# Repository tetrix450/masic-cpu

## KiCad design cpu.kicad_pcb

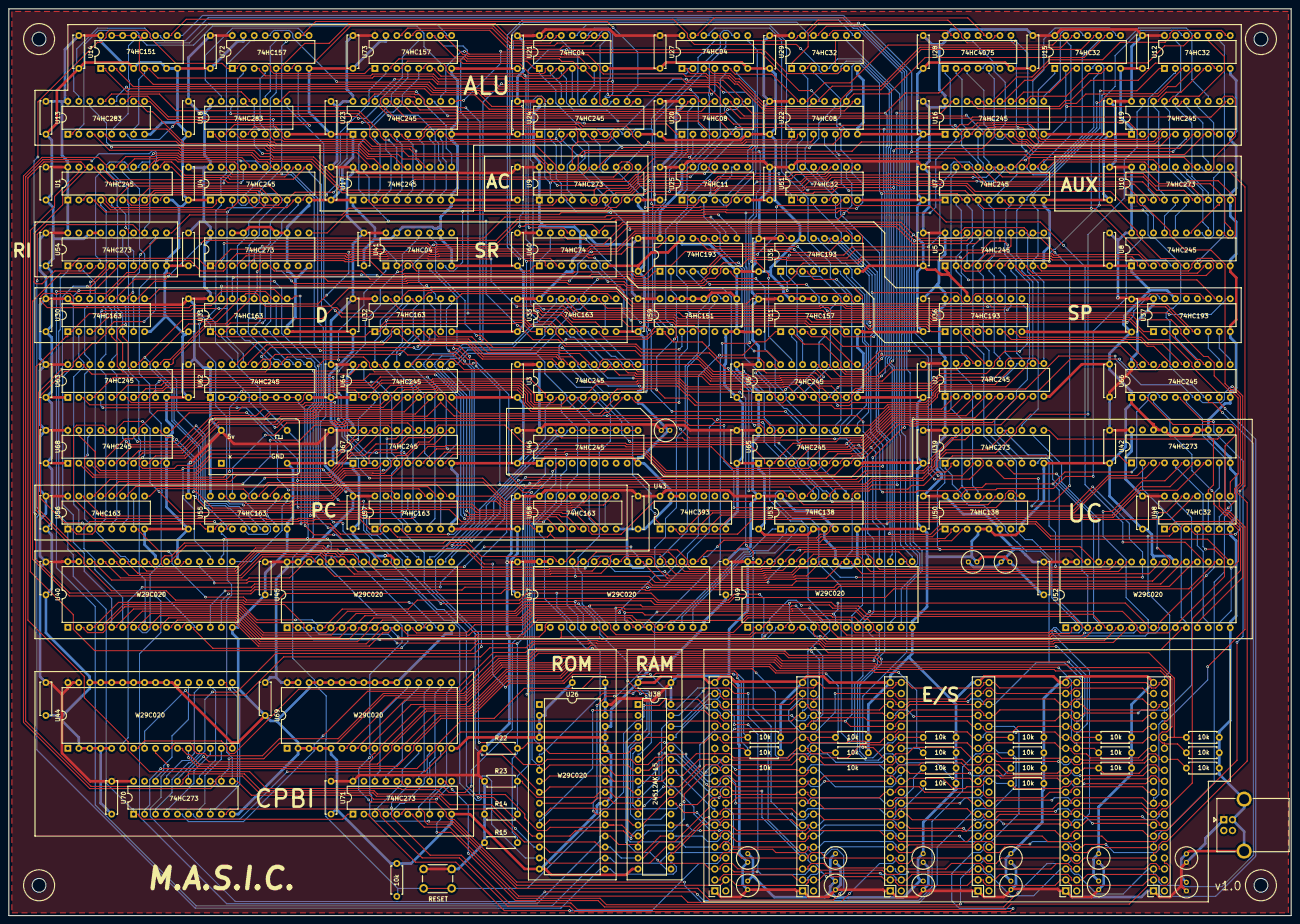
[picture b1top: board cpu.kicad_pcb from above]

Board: 2 copper layers, 297.0 x 210.0 mm, 197 parts (0 on the bottom side), 317 nets.

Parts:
C1, C2, C3, C4, C5, C6, C7, C8, C9, C10, C11, C12, C13, C14, C15, C16, C17, C18, C19, C20, C21, C22, C23, C24, C25, C26, C27, C28, C29, C30, C31, C32, C33, C34, C35, C36, C37, C39, C40, C41, C42, C43, C44, C45, C46, C47, C49, C50, C51, C52, C53, C54, C55, C56, C57, C58, C59, C60, C61, C62, C63, C64, C65, C66, C67, C68, C69, C70, C79, C84, C87, C88, C89: 100n; C_Disc_7.62mm
C38, C71, C72, C73, C74, C80, C81, C85: 1u; C_Radial_D5.0mm_H5.0mm_P2.00mm
C75, C76, C77, C78, C82, C83, C86: 10u; C_Radial_D5.0mm_H5.0mm_P2.00mm
H1, H2, H3, H4: MountingHole; MountingHole_3.2mm_M3
J0, J1, J2, J3, J4, J5: Conn_02x20_Counter_Clockwise; PinSocket_2x20_P2.54mm_Vertical
J9: USB_B; USB_B_OST_USB-B1HSxx_Horizontal
R1, R2, R3, R4, R5, R6, R7, R8, R9, R10, R11, R12, R13, R16, R17, R18, R19, R20, R21, R22, R23: 10k; R_Axial_DIN0207_L6.3mm_D2.5mm_P7.62mm_Horizontal
R14, R15: 1k; R_Axial_DIN0207_L6.3mm_D2.5mm_P7.62mm_Horizontal
SW1: SW_Push; SW_PUSH_6mm
U1, U2, U3, U4, U5, U6, U7, U8, U16, U17, U19, U23, U24, U46, U62, U63, U64, U65, U66, U67, U68: 74HC245; DIP-20_W7.62mm
U9, U10, U39, U42, U54, U61, U70, U71: 74HC273; DIP-20_W7.62mm
U11: 74HC157; DIP-16_W7.62mm
U12, U15, U29, U48, U51: 74HC32; DIP-14_W7.62mm
U13, U18: 74HC283; DIP-16_W7.62mm
U14, U59: 74HC151; DIP-16_W7.62mm
U20, U22: 74HC08; DIP-14_W7.62mm
U21, U27, U41: 74HC04; DIP-14_W7.62mm
U25: 74HC11; DIP-14_W7.62mm
U26, U40, U44, U45, U47, U49, U52, U69: W29C020; DIP-32_W15.24mm
U28: 74HC4075; DIP-14_W7.62mm
U30, U31, U32, U33, U55, U56, U57, U58: 74HC163; DIP-16_W7.62mm
U34, U35, U36, U37: 74HC193; DIP-16_W7.62mm
U38: 24512AK-15; DIP-32_W7.62mm
U43: 74LS393; DIP-14_W7.62mm
U50, U53: 74HC138; DIP-16_W7.62mm
U60: 74HC74; DIP-14_W7.62mm
U72, U73: 74LS157; DIP-16_W7.62mm
X1: 4MHz; Oscillator_DIP-14

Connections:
+5V: C1.1, C2.1, C3.1, C4.1, C5.1, C6.1, C7.1, C8.1, C9.1, C10.1, C11.1, C12.1, C13.1, C14.1, C15.1, C16.1, C17.1, C18.1, C19.1, C20.1, C21.1, C22.1, C23.1, C24.1, C25.1, C26.1, C27.1, C28.1, C29.1, C30.1, C31.1, C32.1, C33.1, C34.1, C35.1, C36.1, C37.1, C38.1, C39.1, C40.1, C41.1, C42.2, C43.1, C44.1, C45.1, C46.2, C47.1, C49.2, C50.1, C51.1, C52.1, C53.1, C54.1, C55.1, C56.1, C57.1, C58.1, C59.1, C60.1, C61.1, C62.1, C63.1, C64.1, C65.1, C66.1, C67.1, C68.1, C69.1, C70.1, C71.1, C72.1, C73.1, C74.1, C75.1, C76.1, C77.1, C78.1, C79.2, C80.1, C81.1, C82.1, C83.1, C84.1, C85.1, C86.1, C87.1, C88.1, C89.1, J0.1, J1.1, J2.1, J3.1, J4.1, J5.1, J9.1 (VBUS), R14.1, R15.1, R22.1, R23.1, SW1.1, U1.1 (A->B), U1.20 (VCC), U2.1 (A->B), U2.20 (VCC), U3.1 (A->B), U3.20 (VCC), U4.20 (VCC), U5.20 (VCC), U6.1 (A->B), U6.20 (VCC), U7.20 (VCC), U8.20 (VCC), U9.1 (~Mr), U9.20 (VCC), U10.1 (~Mr), U10.20 (VCC), U11.16 (VCC), U12.14 (VCC), U13.16 (VCC), U14.3 (I1), U14.16 (VCC), U15.14 (VCC), U16.20 (VCC), U17.20 (VCC), U18.16 (VCC), U19.20 (VCC), U20.14 (VCC), U21.14 (VCC), U22.14 (VCC), U23.20 (VCC), U24.20 (VCC), U25.14 (VCC), U26.31 (~WE), U26.32 (VDD), U27.14 (VCC), U28.14 (VDD), U29.14 (VCC), U30.16 (VCC), U31.16 (VCC), U32.16 (VCC), U33.16 (VCC), U34.16 (VCC), U35.16 (VCC), U36.16 (VCC), U37.16 (VCC), U38.32 (VDD), U39.20 (VCC), U40.31 (~WE), U40.32 (VDD), U41.14 (VCC), U42.20 (VCC), U43.14 (VCC), U44.31 (~WE), U44.32 (VDD), U45.31 (~WE), U45.32 (VDD), U46.20 (VCC), U47.31 (~WE), U47.32 (VDD), U48.14 (VCC), U49.31 (~WE), U49.32 (VDD), U50.6 (E3), U50.16 (VCC), U51.14 (VCC), U52.31 (~WE), U52.32 (VDD), U53.6 (E3), U53.16 (VCC), U54.20 (VCC), U55.16 (VCC), U56.16 (VCC), U57.16 (VCC), U58.16 (VCC), U59.16 (VCC), U60.4 (~S), U60.10 (~S), U60.14 (VCC), U61.20 (VCC), U62.1 (A->B), U62.20 (VCC), U63.20 (VCC), U64.20 (VCC), U65.20 (VCC), U66.20 (VCC), U67.20 (VCC), U68.20 (VCC), U69.31 (~WE), U69.32 (VDD), U70.20 (VCC), U71.20 (VCC), U72.16 (VCC), U73.16 (VCC), X1.14 (Vcc)
/CLK: J0.40, J1.40, J2.40, J3.40, J4.40, J5.40, U29.2, U29.5, U29.10, U30.2 (CP), U31.2 (CP), U32.2 (CP), U33.2 (CP), U39.11 (Cp), U41.11, U42.11 (Cp), U48.2, U48.5, U48.10, U51.5, U51.13, U55.2 (CP), U56.2 (CP), U57.2 (CP), U58.2 (CP), U70.11 (Cp), U71.11 (Cp), X1.8 (OUT)
/CPBI/BACK0: J0.32, U70.2 (Q0)
/CPBI/BACK1: J1.32, U70.5 (Q1)
/CPBI/BACK2: J2.32, U70.6 (Q2)
/CPBI/BACK3: J3.32, U70.9 (Q3)
/CPBI/BACK4: J4.32, U70.12 (Q4)
/CPBI/BACK5: J5.32, U70.15 (Q5)
/CPBI/BRQ0: J0.30, R9.1, U44.12 (A0)
/CPBI/BRQ1: J1.30, R8.1, U44.11 (A1)
/CPBI/BRQ2: J2.30, R10.1, U44.10 (A2)
/CPBI/BRQ3: J3.30, R11.1, U44.9 (A3)
/CPBI/BRQ4: J4.30, R12.1, U44.8 (A4)
/CPBI/BRQ5: J5.30, R13.1, U44.7 (A5)
/CPBI/CPUBRQ: U39.14 (D5), U70.16 (Q6)
/CPBI/CPUIRQ: U39.17 (D6), U71.16 (Q6)
/CPBI/IACK0: J0.8, U71.2 (Q0)
/CPBI/IACK1: J1.8, U71.5 (Q1)
/CPBI/IACK2: J2.8, U71.6 (Q2)
/CPBI/IACK3: J3.8, U71.9 (Q3)
/CPBI/IACK4: J4.8, U71.12 (Q4)
/CPBI/IACK5: J5.8, U71.15 (Q5)
/CPBI/IRQ0: J0.28, R3.1, U69.12 (A0)
/CPBI/IRQ1: J1.28, R2.1, U69.11 (A1)
/CPBI/IRQ2: J2.28, R4.1, U69.10 (A2)
/CPBI/IRQ3: J3.28, R5.1, U69.9 (A3)
/CPBI/IRQ4: J4.28, R6.1, U69.8 (A4)
/CPBI/IRQ5: J5.28, R7.1, U69.7 (A5)
/CPU/AC_0: U7.18 (B0), U9.2 (Q0), U10.3 (D0), U12.2, U13.5 (A1), U14.12 (I7), U14.13 (I6), U14.14 (I5), U14.15 (I4), U20.2
/CPU/AC_1: U7.17 (B1), U9.5 (Q1), U10.4 (D1), U12.5, U13.3 (A2), U19.18 (B0), U20.5
/CPU/AC_2: U7.16 (B2), U9.6 (Q2), U10.7 (D2), U12.10, U13.14 (A3), U19.17 (B1), U20.10
/CPU/AC_3: U7.15 (B3), U9.9 (Q3), U10.8 (D3), U12.13, U13.12 (A4), U19.16 (B2), U20.13
/CPU/AC_4: U7.14 (B4), U9.12 (Q4), U10.13 (D4), U15.2, U18.5 (A1), U19.15 (B3), U22.2
/CPU/AC_5: U7.13 (B5), U9.15 (Q5), U10.14 (D5), U15.5, U18.3 (A2), U19.14 (B4), U22.5
/CPU/AC_6: U7.12 (B6), U9.16 (Q6), U10.17 (D6), U15.10, U18.14 (A3), U19.13 (B5), U22.10
/CPU/AC_7: U7.11 (B7), U9.19 (Q7), U10.18 (D7), U14.1 (I3), U15.13, U18.12 (A4), U19.12 (B6), U22.13, U25.13, U27.5
/CPU/ALU/NOT_0: U21.2, U24.18 (B0), U73.3 (I1a)
/CPU/ALU/NOT_1: U21.4, U24.17 (B1), U73.6 (I1b)
/CPU/ALU/NOT_2: U21.6, U24.16 (B2), U73.10 (I1c)
/CPU/ALU/NOT_3: U21.8, U24.15 (B3), U73.13 (I1d)
/CPU/ALU/NOT_4: U21.10, U24.14 (B4), U72.3 (I1a)
/CPU/ALU/NOT_5: U21.12, U24.13 (B5), U72.6 (I1b)
/CPU/ALU/NOT_6: U24.12 (B6), U27.2, U72.10 (I1c)
/CPU/ALU/NOT_7: U24.11 (B7), U27.4, U72.13 (I1d)
/CPU/ALU/TO_AC_0: U6.18 (B0), U9.3 (D0), U16.2 (A0), U17.2 (A0), U19.2 (A0), U23.2 (A0), U24.2 (A0), U28.1
/CPU/ALU/TO_AC_1: U6.17 (B1), U9.4 (D1), U16.3 (A1), U17.3 (A1), U19.3 (A1), U23.3 (A1), U24.3 (A1), U28.2
/CPU/ALU/TO_AC_2: U6.16 (B2), U9.7 (D2), U16.4 (A2), U17.4 (A2), U19.4 (A2), U23.4 (A2), U24.4 (A2), U28.8
/CPU/ALU/TO_AC_3: U6.15 (B3), U9.8 (D3), U16.5 (A3), U17.5 (A3), U19.5 (A3), U23.5 (A3), U24.5 (A3), U28.3
/CPU/ALU/TO_AC_4: U6.14 (B4), U9.13 (D4), U16.6 (A4), U17.6 (A4), U19.6 (A4), U23.6 (A4), U24.6 (A4), U28.4
/CPU/ALU/TO_AC_5: U6.13 (B5), U9.14 (D5), U16.7 (A5), U17.7 (A5), U19.7 (A5), U23.7 (A5), U24.7 (A5), U28.5
/CPU/ALU/TO_AC_6: U6.12 (B6), U9.17 (D6), U16.8 (A6), U17.8 (A6), U19.8 (A6), U23.8 (A6), U24.8 (A6), U29.12
/CPU/ALU/TO_ADDER_0: U13.6 (B1), U73.4 (Za)
/CPU/ALU/TO_ADDER_1: U13.2 (B2), U73.7 (Zb)
/CPU/ALU/TO_ADDER_2: U13.15 (B3), U73.9 (Zc)
/CPU/ALU/TO_ADDER_3: U13.11 (B4), U73.12 (Zd)
/CPU/ALU/TO_ADDER_4: U18.6 (B1), U72.4 (Za)
/CPU/ALU/TO_ADDER_5: U18.2 (B2), U72.7 (Zb)
/CPU/ALU/TO_ADDER_6: U18.15 (B3), U72.9 (Zc)
/CPU/ALU/TO_ADDER_7: U18.11 (B4), U72.12 (Zd)
/CPU/ALU_C: U18.9 (C4), U59.3 (I1), U59.4 (I0)
/CPU/ALU_O: U11.6 (I1b), U51.3
/CPU/ALU_S: U6.11 (B7), U9.18 (D7), U11.3 (I1a), U16.9 (A7), U17.9 (A7), U19.9 (A7), U23.9 (A7), U24.9 (A7), U25.3, U27.11, U29.13
/CPU/ALU_Z: U11.10 (I1c), U27.12
/CPU/AUX0: U8.18 (B0), U10.2 (Q0)
/CPU/AUX1: U8.17 (B1), U10.5 (Q1)
/CPU/AUX2: U8.16 (B2), U10.6 (Q2)
/CPU/AUX3: U8.15 (B3), U10.9 (Q3)
/CPU/AUX4: U8.14 (B4), U10.12 (Q4)
/CPU/AUX5: U8.13 (B5), U10.15 (Q5)
/CPU/AUX6: U8.12 (B6), U10.16 (Q6)
/CPU/AUX7: U8.11 (B7), U10.19 (Q7)
/CPU/BACK: U44.6 (A6), U52.21 (DQ7)
/CPU/BUS_0: U1.2 (A0), U2.18 (B0), U3.18 (B0), U4.2 (A0), U5.2 (A0), U6.2 (A0), U7.2 (A0), U8.2 (A0), U15.12, U22.12, U25.2, U27.3, U27.9, U30.3 (D0), U32.3 (D0), U59.1 (I3), U62.18 (B0), U72.14 (I0d)
/CPU/BUS_1: U1.3 (A1), U2.17 (B1), U3.17 (B1), U4.3 (A1), U5.3 (A1), U6.3 (A1), U7.3 (A1), U8.3 (A1), U11.2 (I0a), U15.9, U22.9, U27.1, U30.4 (D1), U32.4 (D1), U62.17 (B1), U72.11 (I0c)
/CPU/BUS_2: U1.4 (A2), U2.16 (B2), U3.16 (B2), U4.4 (A2), U5.4 (A2), U6.4 (A2), U7.4 (A2), U8.4 (A2), U11.5 (I0b), U15.4, U21.13, U22.4, U30.5 (D2), U32.5 (D2), U62.16 (B2), U72.5 (I0b)
/CPU/BUS_3: U1.5 (A3), U2.15 (B3), U3.15 (B3), U4.5 (A3), U5.5 (A3), U6.5 (A3), U7.5 (A3), U8.5 (A3), U11.11 (I0c), U15.1, U21.11, U22.1, U30.6 (D3), U32.6 (D3), U62.15 (B3), U72.2 (I0a)
/CPU/BUS_4: U1.6 (A4), U2.14 (B4), U3.14 (B4), U4.6 (A4), U5.6 (A4), U6.6 (A4), U7.6 (A4), U8.6 (A4), U12.12, U20.12, U21.9, U31.3 (D0), U33.3 (D0), U60.2 (D), U62.14 (B4), U73.14 (I0d)
/CPU/BUS_5: U1.7 (A5), U2.13 (B5), U3.13 (B5), U4.7 (A5), U5.7 (A5), U6.7 (A5), U7.7 (A5), U8.7 (A5), U12.9, U20.9, U21.5, U31.4 (D1), U33.4 (D1), U62.13 (B5), U73.11 (I0c)
/CPU/BUS_6: U1.8 (A6), U2.12 (B6), U3.12 (B6), U4.8 (A6), U5.8 (A6), U6.8 (A6), U7.8 (A6), U8.8 (A6), U12.4, U20.4, U21.3, U31.5 (D2), U33.5 (D2), U62.12 (B6), U73.5 (I0b)
/CPU/BUS_7: U1.9 (A7), U2.11 (B7), U3.11 (B7), U4.9 (A7), U5.9 (A7), U6.9 (A7), U7.9 (A7), U8.9 (A7), U12.1, U20.1, U21.1, U31.6 (D3), U33.6 (D3), U59.2 (I2), U62.11 (B7), U73.2 (I0a)
/CPU/C_FLAG: U5.18 (B0), U14.2 (I2), U39.3 (D0), U60.9 (Q)
/CPU/D0: U30.14 (Q0), U34.15 (A), U56.3 (D0), U63.18 (B0)
/CPU/D1: U30.13 (Q1), U34.1 (B), U56.4 (D1), U63.17 (B1)
/CPU/D2: U30.12 (Q2), U34.10 (C), U56.5 (D2), U63.16 (B2)
/CPU/D3: U30.11 (Q3), U34.9 (D), U56.6 (D3), U63.15 (B3)
/CPU/D4: U31.14 (Q0), U35.15 (A), U55.3 (D0), U63.14 (B4)
/CPU/D5: U31.13 (Q1), U35.1 (B), U55.4 (D1), U63.13 (B5)
/CPU/D6: U31.12 (Q2), U35.10 (C), U55.5 (D2), U63.12 (B6)
/CPU/D7: U31.11 (Q3), U35.9 (D), U55.6 (D3), U63.11 (B7)
/CPU/D8: U32.14 (Q0), U36.15 (A), U57.3 (D0), U64.18 (B0)
/CPU/D9: U32.13 (Q1), U36.1 (B), U57.4 (D1), U64.17 (B1)
/CPU/D10: U32.12 (Q2), U36.10 (C), U57.5 (D2), U64.16 (B2)
/CPU/D11: U32.11 (Q3), U36.9 (D), U57.6 (D3), U64.15 (B3)
/CPU/D12: U33.14 (Q0), U37.15 (A), U58.3 (D0), U64.14 (B4)
/CPU/D13: U33.13 (Q1), U37.1 (B), U58.4 (D1), U64.13 (B5)
/CPU/D14: U33.12 (Q2), U37.10 (C), U58.5 (D2), U64.12 (B6)
/CPU/D15: U33.11 (Q3), U37.9 (D), U58.6 (D3), U64.11 (B7)
/CPU/DAT_0: J0.26, J1.26, J2.26, J3.26, J4.26, J5.26, R21.1, U1.18 (B0), U4.18 (B0), U26.21 (DQ7), U38.13 (DQ0), U54.3 (D0)
/CPU/DAT_1: J0.24, J1.24, J2.24, J3.24, J4.24, J5.24, R20.1, U1.17 (B1), U4.17 (B1), U26.20 (DQ6), U38.14 (DQ1), U54.4 (D1)
/CPU/DAT_2: J0.22, J1.22, J2.22, J3.22, J4.22, J5.22, R19.1, U1.16 (B2), U4.16 (B2), U26.19 (DQ5), U38.15 (DQ2), U54.7 (D2)
/CPU/DAT_3: J0.18, J1.18, J2.18, J3.18, J4.18, J5.18, R18.1, U1.15 (B3), U4.15 (B3), U26.18 (DQ4), U38.17 (DQ3), U54.8 (D3)
/CPU/DAT_4: J0.16, J1.16, J2.16, J3.16, J4.16, J5.16, R17.1, U1.14 (B4), U4.14 (B4), U26.17 (DQ3), U38.18 (DQ4), U54.13 (D4)
/CPU/DAT_5: J0.14, J1.14, J2.14, J3.14, J4.14, J5.14, R16.1, U1.13 (B5), U4.13 (B5), U26.15 (DQ2), U38.19 (DQ5), U54.14 (D5)
/CPU/DAT_6: J0.12, J1.12, J2.12, J3.12, J4.12, J5.12, U1.12 (B6), U4.12 (B6), U26.14 (DQ1), U38.20 (DQ6)
/CPU/DAT_7: J0.10, J1.10, J2.10, J3.10, J4.10, J5.10, U1.11 (B7), U4.11 (B7), U26.13 (DQ0), U38.21 (DQ7)
/CPU/DIR_0: J0.33, J1.33, J2.33, J3.33, J4.33, J5.33, U2.2 (A0), U26.12 (A0), U38.12 (A0), U63.2 (A0), U65.2 (A0), U67.2 (A0)
/CPU/DIR_1: J0.31, J1.31, J2.31, J3.31, J4.31, J5.31, U2.3 (A1), U26.11 (A1), U38.11 (A1), U63.3 (A1), U65.3 (A1), U67.3 (A1)
/CPU/DIR_2: J0.29, J1.29, J2.29, J3.29, J4.29, J5.29, U2.4 (A2), U26.10 (A2), U38.10 (A2), U63.4 (A2), U65.4 (A2), U67.4 (A2)
/CPU/DIR_3: J0.27, J1.27, J2.27, J3.27, J4.27, J5.27, U2.5 (A3), U26.9 (A3), U38.9 (A3), U63.5 (A3), U65.5 (A3), U67.5 (A3)
/CPU/DIR_4: J0.25, J1.25, J2.25, J3.25, J4.25, J5.25, U2.6 (A4), U26.8 (A4), U38.8 (A4), U63.6 (A4), U65.6 (A4), U67.6 (A4)
/CPU/DIR_5: J0.23, J1.23, J2.23, J3.23, J4.23, J5.23, U2.7 (A5), U26.7 (A5), U38.7 (A5), U63.7 (A5), U65.7 (A5), U67.7 (A5)
/CPU/DIR_6: J0.21, J1.21, J2.21, J3.21, J4.21, J5.21, U2.8 (A6), U26.6 (A6), U38.6 (A6), U63.8 (A6), U65.8 (A6), U67.8 (A6)
/CPU/DIR_7: J0.19, J1.19, J2.19, J3.19, J4.19, J5.19, U2.9 (A7), U26.5 (A7), U38.5 (A7), U63.9 (A7), U65.9 (A7), U67.9 (A7)
/CPU/DIR_8: J0.17, J1.17, J2.17, J3.17, J4.17, J5.17, U3.2 (A0), U26.27 (A8), U38.27 (A8), U64.2 (A0), U66.2 (A0), U68.2 (A0)
/CPU/DIR_9: J0.15, J1.15, J2.15, J3.15, J4.15, J5.15, U3.3 (A1), U26.26 (A9), U38.26 (A9), U64.3 (A1), U66.3 (A1), U68.3 (A1)
/CPU/DIR_10: J0.13, J1.13, J2.13, J3.13, J4.13, J5.13, U3.4 (A2), U38.23 (A10), U64.4 (A2), U66.4 (A2), U68.4 (A2)
/CPU/DIR_11: J0.11, J1.11, J2.11, J3.11, J4.11, J5.11, U3.5 (A3), U38.25 (A11), U64.5 (A3), U66.5 (A3), U68.5 (A3)
/CPU/DIR_12: J0.9, J1.9, J2.9, J3.9, J4.9, J5.9, U3.6 (A4), U38.4 (A12), U64.6 (A4), U66.6 (A4), U68.6 (A4)
/CPU/DIR_13: J0.7, J1.7, J2.7, J3.7, J4.7, J5.7, U3.7 (A5), U25.11, U38.28 (A13), U64.7 (A5), U66.7 (A5), U68.7 (A5)
/CPU/DIR_14: J0.5, J1.5, J2.5, J3.5, J4.5, J5.5, U3.8 (A6), U25.10, U38.3 (A14), U64.8 (A6), U66.8 (A6), U68.8 (A6)
/CPU/DIR_15: J0.3, J1.3, J2.3, J3.3, J4.3, J5.3, U3.9 (A7), U25.9, U38.31 (A15), U64.9 (A7), U66.9 (A7), U68.9 (A7)
/CPU/FILL_BIT: U45.14 (DQ1), U62.2 (A0), U62.3 (A1), U62.4 (A2), U62.5 (A3), U62.6 (A4), U62.7 (A5), U62.8 (A6), U62.9 (A7)
/CPU/F_AC: U9.11 (Cp), U48.6
/CPU/F_AUX: U10.11 (Cp), U48.3
/CPU/F_C: U29.6, U60.11 (C)
/CPU/F_DH: U32.9 (~PE), U33.9 (~PE), U45.19 (DQ5)
/CPU/F_DL: U30.9 (~PE), U31.9 (~PE), U45.20 (DQ6)
/CPU/F_D_UP: U30.7 (CEP), U30.10 (CET), U52.18 (DQ4)
/CPU/F_I: U29.8, U60.3 (C)
/CPU/F_PC: U40.17 (DQ3), U55.9 (~PE), U56.9 (~PE), U57.9 (~PE), U58.9 (~PE)
/CPU/F_PC_UP: U52.20 (DQ6), U56.7 (CEP), U56.10 (CET)
/CPU/F_RI: U51.11, U54.11 (Cp)
/CPU/F_SP_DOWN: U34.4 (DOWN), U48.8
/CPU/F_SP_UP: U34.5 (UP), U51.6
/CPU/F_ZOS: U29.3, U61.11 (Cp)
/CPU/IACK: U49.13 (DQ0), U69.6 (A6)
/CPU/I_FLAG: U5.11 (B7), U5.12 (B6), U5.13 (B5), U5.14 (B4), U39.13 (D4), U60.5 (Q)
/CPU/MUX C/C: U59.5 (Z), U60.12 (D)
/CPU/MUX ZOS/O: U11.7 (Zb), U61.4 (D1)
/CPU/MUX ZOS/S: U11.4 (Za), U61.3 (D0)
/CPU/MUX ZOS/Z: U11.9 (Zc), U61.7 (D2)
/CPU/MUX_ADD: U40.13 (DQ0), U72.1 (S), U73.1 (S)
/CPU/MUX_CI_0: U14.11 (S0), U49.18 (DQ4)
/CPU/MUX_CI_1: U14.10 (S1), U49.19 (DQ5)
/CPU/MUX_CI_2: U14.9 (S2), U49.20 (DQ6)
/CPU/MUX_C_0: U47.20 (DQ6), U59.10 (S1)
/CPU/MUX_C_1: U47.21 (DQ7), U59.11 (S0)
/CPU/MUX_ZOS: U11.1 (S), U45.13 (DQ0)
/CPU/O_FLAG: U5.16 (B2), U39.7 (D2), U61.5 (Q1)
/CPU/PC_0: U56.14 (Q0), U67.18 (B0)
/CPU/PC_1: U56.13 (Q1), U67.17 (B1)
/CPU/PC_2: U56.12 (Q2), U67.16 (B2)
/CPU/PC_3: U56.11 (Q3), U67.15 (B3)
/CPU/PC_4: U55.14 (Q0), U67.14 (B4)
/CPU/PC_5: U55.13 (Q1), U67.13 (B5)
/CPU/PC_6: U55.12 (Q2), U67.12 (B6)
/CPU/PC_7: U55.11 (Q3), U67.11 (B7)
/CPU/PC_8: U57.14 (Q0), U68.18 (B0)
/CPU/PC_9: U57.13 (Q1), U68.17 (B1)
/CPU/PC_10: U57.12 (Q2), U68.16 (B2)
/CPU/PC_11: U57.11 (Q3), U68.15 (B3)
/CPU/PC_12: U58.14 (Q0), U68.14 (B4)
/CPU/PC_13: U58.13 (Q1), U68.13 (B5)
/CPU/PC_14: U58.12 (Q2), U68.12 (B6)
/CPU/PC_15: U58.11 (Q3), U68.11 (B7)
/CPU/RI0: U40.26 (A9), U45.26 (A9), U47.26 (A9), U49.26 (A9), U52.26 (A9), U54.2 (Q0)
/CPU/RI1: U40.27 (A8), U45.27 (A8), U47.27 (A8), U49.27 (A8), U52.27 (A8), U54.5 (Q1)
/CPU/RI2: U40.5 (A7), U45.5 (A7), U47.5 (A7), U49.5 (A7), U52.5 (A7), U54.6 (Q2)
/CPU/RI3: U40.6 (A6), U45.6 (A6), U47.6 (A6), U49.6 (A6), U52.6 (A6), U54.9 (Q3)
/CPU/RI4: U40.7 (A5), U45.7 (A5), U47.7 (A5), U49.7 (A5), U52.7 (A5), U54.12 (Q4)
/CPU/RI5: U40.8 (A4), U45.8 (A4), U47.8 (A4), U49.8 (A4), U52.8 (A4), U54.15 (Q5)
/CPU/SP_0: U34.3 (QA), U65.18 (B0)
/CPU/SP_1: U34.2 (QB), U65.17 (B1)
/CPU/SP_2: U34.6 (QC), U65.16 (B2)
/CPU/SP_3: U34.7 (QD), U65.15 (B3)
/CPU/SP_4: U35.3 (QA), U65.14 (B4)
/CPU/SP_5: U35.2 (QB), U65.13 (B5)
/CPU/SP_6: U35.6 (QC), U65.12 (B6)
/CPU/SP_7: U35.7 (QD), U65.11 (B7)
/CPU/SP_8: U36.3 (QA), U66.18 (B0)
/CPU/SP_9: U36.2 (QB), U66.17 (B1)
/CPU/SP_10: U36.6 (QC), U66.16 (B2)
/CPU/SP_11: U36.7 (QD), U66.15 (B3)
/CPU/SP_12: U37.3 (QA), U66.14 (B4)
/CPU/SP_13: U37.2 (QB), U66.13 (B5)
/CPU/SP_14: U37.6 (QC), U66.12 (B6)
/CPU/SP_15: U37.7 (QD), U66.11 (B7)
/CPU/S_FLAG: U5.17 (B1), U39.4 (D1), U61.2 (Q0)
/CPU/Unidad de control/BUS_DIS: U46.19 (CE), U49.21 (DQ7)
/CPU/Unidad de control/IFETCH: U39.18 (D7), U40.21 (DQ7)
/CPU/Unidad de control/RCF_0: U42.3 (D0), U43.3 (Q0)
/CPU/Unidad de control/RCF_1: U42.4 (D1), U43.4 (Q1)
/CPU/Unidad de control/RCF_2: U42.7 (D2), U43.5 (Q2)
/CPU/Unidad de control/RCF_3: U42.8 (D3), U43.6 (Q3)
/CPU/Unidad de control/RCF_CLR: U40.20 (DQ6), U48.12
/CPU/Unidad de control/S_AC_0: U47.13 (DQ0), U53.1 (A0)
/CPU/Unidad de control/S_AC_1: U47.14 (DQ1), U53.2 (A1)
/CPU/Unidad de control/S_AC_2: U47.15 (DQ2), U53.3 (A2)
/CPU/Unidad de control/S_DAT_0: U47.17 (DQ3), U50.1 (A0)
/CPU/Unidad de control/S_DAT_1: U47.18 (DQ4), U50.2 (A1)
/CPU/Unidad de control/S_DAT_2: U47.19 (DQ5), U50.3 (A2)
/CPU/Unidad de control/~AC_LOAD: U48.4, U52.14 (DQ1)
/CPU/Unidad de control/~AUX_LOAD: U48.1, U52.15 (DQ2)
/CPU/Unidad de control/~LOAD_C: U29.4, U49.14 (DQ1)
/CPU/Unidad de control/~LOAD_I: U29.9, U49.17 (DQ3)
/CPU/Unidad de control/~LOAD_ZOS: U29.1, U49.15 (DQ2)
/CPU/Unidad de control/~RI_LOAD: U51.12, U52.17 (DQ3)
/CPU/Unidad de control/~SP_DOWN: U48.9, U52.13 (DQ0)
/CPU/Unidad de control/~SP_UP: U51.4, U52.19 (DQ5)
/CPU/Z_FLAG: U5.15 (B3), U39.8 (D3), U61.6 (Q2)
/CPU/~AC_OE: U7.19 (CE), U50.14 (O1)
/CPU/~ADD_OE: U17.19 (CE), U53.15 (O0)
/CPU/~AND_OE: U23.19 (CE), U53.13 (O2)
/CPU/~AUX_OE: U8.19 (CE), U50.15 (O0)
/CPU/~BUS_AC: U6.19 (CE), U53.10 (O5)
/CPU/~DIRH_OE: U3.19 (CE), U50.12 (O3)
/CPU/~DIRL_OE: U2.19 (CE), U50.13 (O2)
/CPU/~D_CLR: U30.1 (~MR), U31.1 (~MR), U32.1 (~MR), U33.1 (~MR), U45.15 (DQ2)
/CPU/~D_OE: U45.21 (DQ7), U63.19 (CE), U64.19 (CE)
/CPU/~EST_OE: U5.19 (CE), U50.10 (O5)
/CPU/~FILL_BUS: U50.9 (O6), U62.19 (CE)
/CPU/~MEM_BUS: U4.19 (CE), U50.11 (O4)
/CPU/~MEM_OE: J0.37, J1.37, J2.37, J3.37, J4.37, J5.37, R14.2, R23.2, U26.24 (~OE), U38.24 (~OE), U46.3 (A1)
/CPU/~MEM_WE: J0.35, J1.35, J2.35, J3.35, J4.35, J5.35, R15.2, R22.2, U1.19 (CE), U38.29 (~WE), U46.2 (A0)
/CPU/~NOT_OE: U24.19 (CE), U53.11 (O4)
/CPU/~OR_OE: U16.19 (CE), U53.12 (O3)
/CPU/~PC_OE: U40.19 (DQ5), U67.19 (CE), U68.19 (CE)
/CPU/~SHR_OE: U19.19 (CE), U53.14 (O1)
/CPU/~SP_LOAD: U34.11 (~LOAD), U35.11 (~LOAD), U36.11 (~LOAD), U37.11 (~LOAD), U40.14 (DQ1)
/CPU/~SP_OE: U40.15 (DQ2), U65.19 (CE), U66.19 (CE)
/Decoficación mapa memoria/~CE_BOOTLOADER: U41.6, U51.10
/Decoficación mapa memoria/~CE_RAM: U25.8, U38.22 (~CE1), U41.5
GND: C1.2, C2.2, C3.2, C4.2, C5.2, C6.2, C7.2, C8.2, C9.2, C10.2, C11.2, C12.2, C13.2, C14.2, C15.2, C16.2, C17.2, C18.2, C19.2, C20.2, C21.2, C22.2, C23.2, C24.2, C25.2, C26.2, C27.2, C28.2, C29.2, C30.2, C31.2, C32.2, C33.2, C34.2, C35.2, C36.2, C37.2, C38.2, C39.2, C40.2, C41.2, C42.1, C43.2, C44.2, C45.2, C46.1, C47.2, C49.1, C50.2, C51.2, C52.2, C53.2, C54.2, C55.2, C56.2, C57.2, C58.2, C59.2, C60.2, C61.2, C62.2, C63.2, C64.2, C65.2, C66.2, C67.2, C68.2, C69.2, C70.2, C71.2, C72.2, C73.2, C74.2, C75.2, C76.2, C77.2, C78.2, C79.1, C80.2, C81.2, C82.2, C83.2, C84.2, C85.2, C86.2, C87.2, C88.2, C89.2, J0.39, J1.39, J2.39, J3.39, J4.39, J5.39, J9.4 (GND), J9.5 (Shield), R1.2, R2.2, R3.2, R4.2, R5.2, R6.2, R7.2, R8.2, R9.2, R10.2, R11.2, R12.2, R13.2, R16.2, R17.2, R18.2, R19.2, R20.2, R21.2, U1.10 (GND), U2.10 (GND), U3.10 (GND), U4.1 (A->B), U4.10 (GND), U5.1 (A->B), U5.10 (GND), U6.10 (GND), U7.1 (A->B), U7.10 (GND), U8.1 (A->B), U8.10 (GND), U9.10 (GND), U10.10 (GND), U11.8 (GND), U11.13 (I1d), U11.14 (I0d), U11.15 (E), U12.7 (GND), U13.8 (GND), U14.4 (I0), U14.7 (~E), U14.8 (GND), U15.7 (GND), U16.1 (A->B), U16.10 (GND), U17.1 (A->B), U17.10 (GND), U18.8 (GND), U19.1 (A->B), U19.10 (GND), U20.7 (GND), U21.7 (GND), U22.7 (GND), U23.1 (A->B), U23.10 (GND), U24.1 (A->B), U24.10 (GND), U25.7 (GND), U26.2 (A16), U26.3 (A15), U26.4 (A12), U26.16 (GND), U26.23 (A10), U26.25 (A11), U26.28 (A13), U26.29 (A14), U26.30 (A17), U27.7 (GND), U28.7 (VSS), U29.7 (GND), U30.8 (GND), U31.8 (GND), U32.8 (GND), U33.8 (GND), U34.8 (GND), U34.14 (CLR), U35.8 (GND), U35.14 (CLR), U36.8 (GND), U36.14 (CLR), U37.8 (GND), U37.14 (CLR), U38.16 (GND), U39.10 (GND), U40.16 (GND), U40.22 (~CE), U40.24 (~OE), U41.7 (GND), U41.9, U41.13, U42.10 (GND), U42.13 (D4), U42.14 (D5), U42.17 (D6), U42.18 (D7), U43.7 (GND), U43.12 (MR), U43.13 (CP), U44.2 (A16), U44.3 (A15), U44.4 (A12), U44.5 (A7), U44.16 (GND), U44.22 (~CE), U44.23 (A10), U44.24 (~OE), U44.25 (A11), U44.26 (A9), U44.27 (A8), U44.28 (A13), U44.29 (A14), U44.30 (A17), U45.16 (GND), U45.22 (~CE), U45.24 (~OE), U46.1 (A->B), U46.10 (GND), U47.16 (GND), U47.22 (~CE), U47.24 (~OE), U48.7 (GND), U49.16 (GND), U49.22 (~CE), U49.24 (~OE), U50.4 (E1), U50.5 (E2), U50.8 (GND), U51.7 (GND), U52.16 (GND), U52.22 (~CE), U52.24 (~OE), U53.4 (E1), U53.5 (E2), U53.8 (GND), U54.10 (GND), U54.17 (D6), U54.18 (D7), U55.8 (GND), U56.8 (GND), U57.8 (GND), U58.8 (GND), U59.7 (~E), U59.8 (GND), U59.9 (S2), U59.12 (I7), U59.13 (I6), U59.14 (I5), U59.15 (I4), U60.7 (GND), U61.8 (D3), U61.10 (GND), U61.13 (D4), U61.14 (D5), U61.17 (D6), U61.18 (D7), U62.10 (GND), U63.1 (A->B), U63.10 (GND), U64.1 (A->B), U64.10 (GND), U65.1 (A->B), U65.10 (GND), U66.1 (A->B), U66.10 (GND), U67.1 (A->B), U67.10 (GND), U68.1 (A->B), U68.10 (GND), U69.2 (A16), U69.3 (A15), U69.4 (A12), U69.5 (A7), U69.16 (GND), U69.22 (~CE), U69.23 (A10), U69.24 (~OE), U69.25 (A11), U69.26 (A9), U69.27 (A8), U69.28 (A13), U69.29 (A14), U69.30 (A17), U70.10 (GND), U71.10 (GND), U72.8 (GND), U72.15 (E), U73.8 (GND), U73.15 (E), X1.7 (GND)
MEM/~IO: J0.6, J1.6, J2.6, J3.6, J4.6, J5.6, U38.30 (CE2), U41.4
unnamed: U13.7 (C0), U14.5 (Z), U19.11 (B7)
unnamed: U13.9 (C4), U18.7 (C0)
unnamed: U13.4 (S1), U17.18 (B0)
unnamed: U13.1 (S2), U17.17 (B1)
unnamed: U13.13 (S3), U17.16 (B2)
unnamed: U13.10 (S4), U17.15 (B3)
unnamed: U12.3, U16.18 (B0)
unnamed: U12.6, U16.17 (B1)
unnamed: U12.8, U16.16 (B2)
unnamed: U12.11, U16.15 (B3)
unnamed: U15.3, U16.14 (B4)
unnamed: U15.6, U16.13 (B5)
unnamed: U15.8, U16.12 (B6)
unnamed: U15.11, U16.11 (B7)
unnamed: U17.14 (B4), U18.4 (S1)
unnamed: U17.13 (B5), U18.1 (S2)
unnamed: U17.12 (B6), U18.13 (S3)
unnamed: U17.11 (B7), U18.10 (S4)
unnamed: U20.3, U23.18 (B0)
unnamed: U20.6, U23.17 (B1)
unnamed: U20.8, U23.16 (B2)
unnamed: U20.11, U23.15 (B3)
unnamed: U22.3, U23.14 (B4)
unnamed: U22.6, U23.13 (B5)
unnamed: U22.8, U23.12 (B6)
unnamed: U22.11, U23.11 (B7)
unnamed: U25.1, U27.10
unnamed: U25.4, U27.8
unnamed: U25.5, U27.6
unnamed: U25.6, U51.2
unnamed: U25.12, U51.1
unnamed: U26.22 (~CE), U51.8
unnamed: U27.13, U28.10
unnamed: U28.9, U28.11
unnamed: U28.6, U28.12
unnamed: U28.13, U29.11
unnamed: U30.15 (TC), U31.7 (CEP), U31.10 (CET)
unnamed: U31.15 (TC), U32.7 (CEP), U32.10 (CET)
unnamed: U32.15 (TC), U33.7 (CEP), U33.10 (CET)
unnamed: U34.13 (~BO), U35.4 (DOWN)
unnamed: U34.12 (~CO), U35.5 (UP)
unnamed: U35.13 (~BO), U36.4 (DOWN)
unnamed: U35.12 (~CO), U36.5 (UP)
unnamed: U36.13 (~BO), U37.4 (DOWN)
unnamed: U36.12 (~CO), U37.5 (UP)
unnamed: U39.2 (Q0), U40.23 (A10), U45.23 (A10), U47.23 (A10), U49.23 (A10), U52.23 (A10)
unnamed: U39.5 (Q1), U40.25 (A11), U45.25 (A11), U47.25 (A11), U49.25 (A11), U52.25 (A11)
unnamed: U39.6 (Q2), U40.4 (A12), U45.4 (A12), U47.4 (A12), U49.4 (A12), U52.4 (A12)
unnamed: U39.9 (Q3), U40.28 (A13), U45.28 (A13), U47.28 (A13), U49.28 (A13), U52.28 (A13)
unnamed: U39.12 (Q4), U40.29 (A14), U45.29 (A14), U47.29 (A14), U49.29 (A14), U52.29 (A14)
unnamed: U39.15 (Q5), U40.3 (A15), U45.3 (A15), U47.3 (A15), U49.3 (A15), U52.3 (A15)
unnamed: U39.16 (Q6), U40.2 (A16), U45.2 (A16), U47.2 (A16), U49.2 (A16), U52.2 (A16)
unnamed: U39.19 (Q7), U40.30 (A17), U45.30 (A17), U47.30 (A17), U49.30 (A17), U52.30 (A17)
unnamed: U40.12 (A0), U42.2 (Q0), U45.12 (A0), U47.12 (A0), U49.12 (A0), U52.12 (A0)
unnamed: U40.11 (A1), U42.5 (Q1), U45.11 (A1), U47.11 (A1), U49.11 (A1), U52.11 (A1)
unnamed: U40.10 (A2), U42.6 (Q2), U45.10 (A2), U47.10 (A2), U49.10 (A2), U52.10 (A2)
unnamed: U40.9 (A3), U42.9 (Q3), U45.9 (A3), U47.9 (A3), U49.9 (A3), U52.9 (A3)
unnamed: U43.2 (MR), U48.11
unnamed: U44.13 (DQ0), U70.3 (D0)
unnamed: U44.14 (DQ1), U70.4 (D1)
unnamed: U44.15 (DQ2), U70.7 (D2)
unnamed: U44.17 (DQ3), U70.8 (D3)
unnamed: U44.18 (DQ4), U70.13 (D4)
unnamed: U44.19 (DQ5), U70.14 (D5)
unnamed: U44.20 (DQ6), U70.17 (D6)
unnamed: U44.21 (DQ7), U70.18 (D7)
unnamed: U45.17 (DQ3), U46.11 (B7), U46.12 (B6), U46.13 (B5), U46.14 (B4), U46.15 (B3), U46.16 (B2), U46.17 (B1)
unnamed: U45.18 (DQ4), U46.18 (B0)
unnamed: U55.7 (CEP), U55.10 (CET), U56.15 (TC)
unnamed: U55.15 (TC), U57.7 (CEP), U57.10 (CET)
unnamed: U57.15 (TC), U58.7 (CEP), U58.10 (CET)
unnamed: U69.13 (DQ0), U71.3 (D0)
unnamed: U69.14 (DQ1), U71.4 (D1)
unnamed: U69.15 (DQ2), U71.7 (D2)
unnamed: U69.17 (DQ3), U71.8 (D3)
unnamed: U69.18 (DQ4), U71.13 (D4)
unnamed: U69.19 (DQ5), U71.14 (D5)
unnamed: U69.20 (DQ6), U71.17 (D6)
unnamed: U69.21 (DQ7), U71.18 (D7)
RESET: J0.34, J1.34, J2.34, J3.34, J4.34, J5.34, R1.1, SW1.2, U41.1, U48.13
~CLK: U41.10, U43.1 (CP)
~MEM/IO: J0.4, J1.4, J2.4, J3.4, J4.4, J5.4, U40.18 (DQ4), U41.3, U51.9
~RESET: J0.36, J1.36, J2.36, J3.36, J4.36, J5.36, U39.1 (~Mr), U41.2, U42.1 (~Mr), U54.1 (~Mr), U55.1 (~MR), U56.1 (~MR), U57.1 (~MR), U58.1 (~MR), U60.1 (~R), U60.13 (~R), U61.1 (~Mr), U70.1 (~Mr), U71.1 (~Mr)
